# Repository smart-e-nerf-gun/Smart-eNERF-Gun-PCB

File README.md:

# Smart-eNERF-Gun-PCB
KiCAD PCB project for the Smart eNERF Gun.

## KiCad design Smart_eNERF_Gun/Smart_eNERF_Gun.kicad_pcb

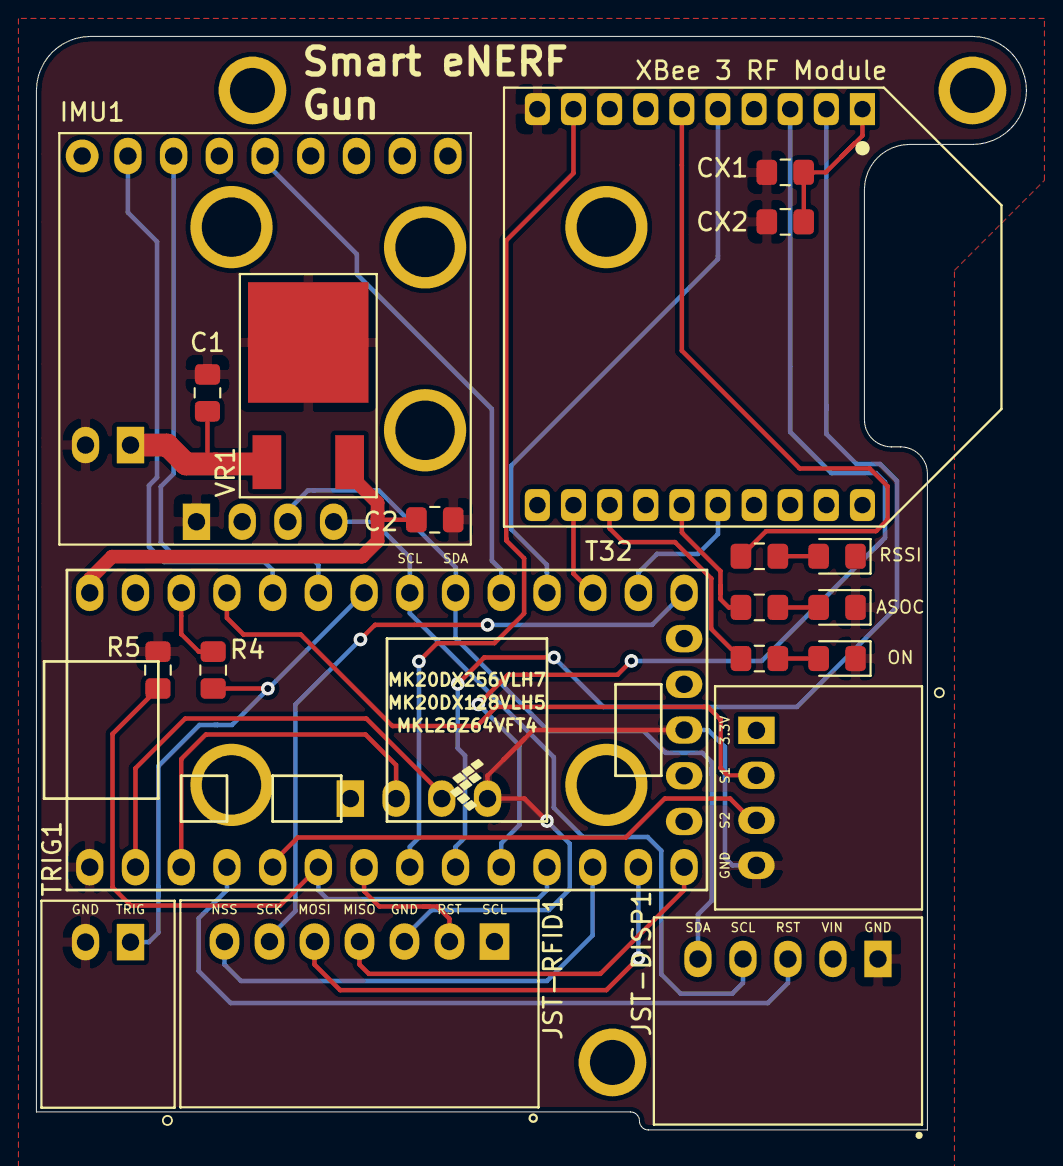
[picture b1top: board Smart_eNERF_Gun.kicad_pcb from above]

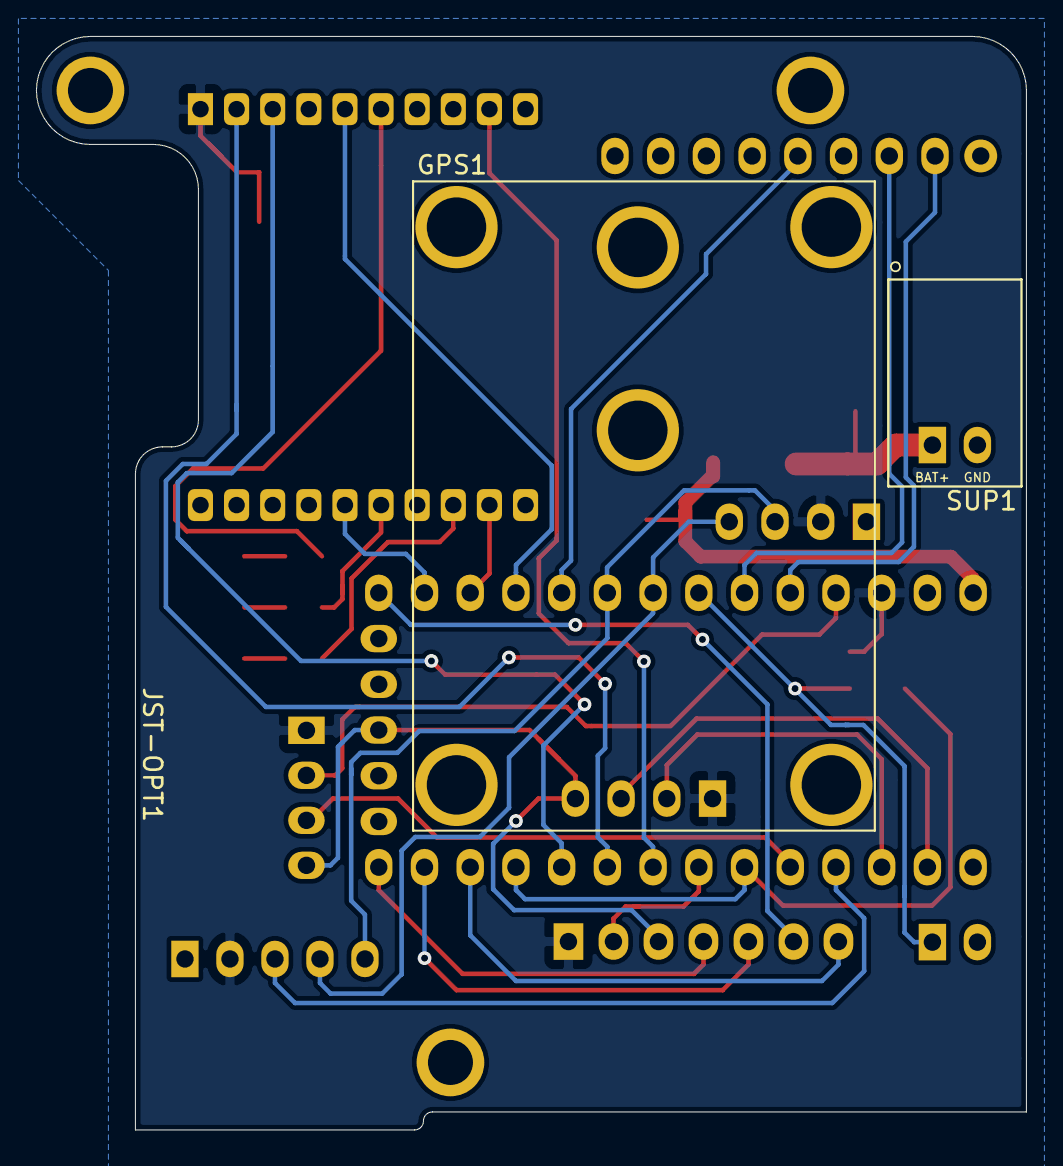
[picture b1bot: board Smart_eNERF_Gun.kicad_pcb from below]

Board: 2 copper layers, 55.0 x 60.8 mm, 25 parts (2 on the bottom side), 33 nets.

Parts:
C1, C2: 2.2uF; C_0805_2012Metric_Pad1.15x1.40mm_HandSolder
CX1: 1.0µF; C_0805_2012Metric_Pad1.15x1.40mm_HandSolder
CX2: 8.2pF; C_0805_2012Metric_Pad1.15x1.40mm_HandSolder
D1, D2, D3: LED; LED_0805_2012Metric_Pad1.15x1.40mm_HandSolder
GPS1: GPS_NEO_6M
H1, H2, H3: MountingHole; Mount_2.5mm
IMU1: LSM9D61; LSM9D61_Breakout
JST-DISP1: S5B-XH-A(LF)(SN); JST_S5B-XH-A(LF)(SN)
JST-OPT1: S4B-XH-A(LF)(SN); JST_S4B-XH-A(LF)(SN)
JST-RFID1: S7B-XH-A(LF)(SN); JST_S7B-XH-A(LF)(SN)
R1, R2, R3: 68; R_0805_2012Metric_Pad1.15x1.40mm_HandSolder
R4: 47k; R_0805_2012Metric_Pad1.15x1.40mm_HandSolder
R5: 1k; R_0805_2012Metric_Pad1.15x1.40mm_HandSolder
SUP1: S2B-XH-A(LF)(SN)_POWER; JST_S2B-XH-A(LF)(SN)
T32: Teensy32; Teensy30_31_32_LC
TRIG1: S2B-XH-A(LF)(SN); JST_S2B-XH-A(LF)(SN)
VR1: BDXXFC0FP-E2; TO-252-3
XBee 3 RF Module: XB3-24Z8PT-J; XCVR_XB3-24Z8PT-J

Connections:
+3V3: CX1.1, CX2.1, GPS1.1, IMU1.2, JST-DISP1.2, JST-OPT1.1, JST-RFID1.1, R4.1, T32.31, XBee 3 RF Module.1
+5V: C2.1, T32.33, VR1.2
+BATT: C1.1, SUP1.1, VR1.1
/DISP-RST: JST-DISP1.3, T32.4
/GPS-2-T32: GPS1.3, T32.2
/I2C-M-RDY: IMU1.9, T32.24
/I2C-SCL: IMU1.4, JST-DISP1.4, T32.26
/I2C-SDA: IMU1.3, JST-DISP1.5, T32.25
/IMU-INT1: IMU1.11, T32.28
/IMU-INT2: IMU1.12, T32.29
/OPT-S1: JST-OPT1.2, T32.30
/OPT-S2: JST-OPT1.3, T32.5
/RFID-MISO: JST-RFID1.4, T32.14
/RFID-MOSI: JST-RFID1.5, T32.13
/RFID-NSS: JST-RFID1.7, T32.12
/RFID-RST: JST-RFID1.2, T32.7
/RFID-SCK: JST-RFID1.6, T32.20
/T32-2-GPS: GPS1.2, T32.3
/T32-2-XB: T32.10, XBee 3 RF Module.3
/TRIG: R4.2, T32.27, TRIG1.1
/XB-2-T32: T32.9, XBee 3 RF Module.2
/XB-ASOC: R3.2, XBee 3 RF Module.15
/XB-CTS_T32-RTS: T32.22, XBee 3 RF Module.12
/XB-ON: R2.2, XBee 3 RF Module.13
/XB-RESET: T32.23, XBee 3 RF Module.5
/XB-RSSI: R1.2, XBee 3 RF Module.6
/XB-RTS_T32-CTS: T32.21, XBee 3 RF Module.16
/XB-WAKE: T32.8, XBee 3 RF Module.9
GND: C1.2, C2.2, CX1.2, CX2.2, D1.1, D2.1, D3.1, GPS1.4, IMU1.1, JST-DISP1.1, JST-OPT1.4, JST-RFID1.3, R5.1, SUP1.2, T32.1, T32.17, TRIG1.2, VR1.PAD, XBee 3 RF Module.10
unnamed: D1.2, R1.1
unnamed: D2.2, R2.1
unnamed: D3.2, R3.1
unnamed: R5.2, T32.6, T32.11

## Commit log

2019-09-25 Bug fix: switch xbee uart pins
2019-09-29 Update routes and silk screen
2019-09-29 Add new symbol and footprint for 9DOF Sensor Stick
2019-09-29 Production 6.2 commit for sensor stick
2019-09-29 Remove generated outputs from repository
2019-10-01 Production
